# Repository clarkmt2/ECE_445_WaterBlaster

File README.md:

# ECE_445_WaterBlaster
Design, Firmware, and Documentation for Fully Electric Water Blaster

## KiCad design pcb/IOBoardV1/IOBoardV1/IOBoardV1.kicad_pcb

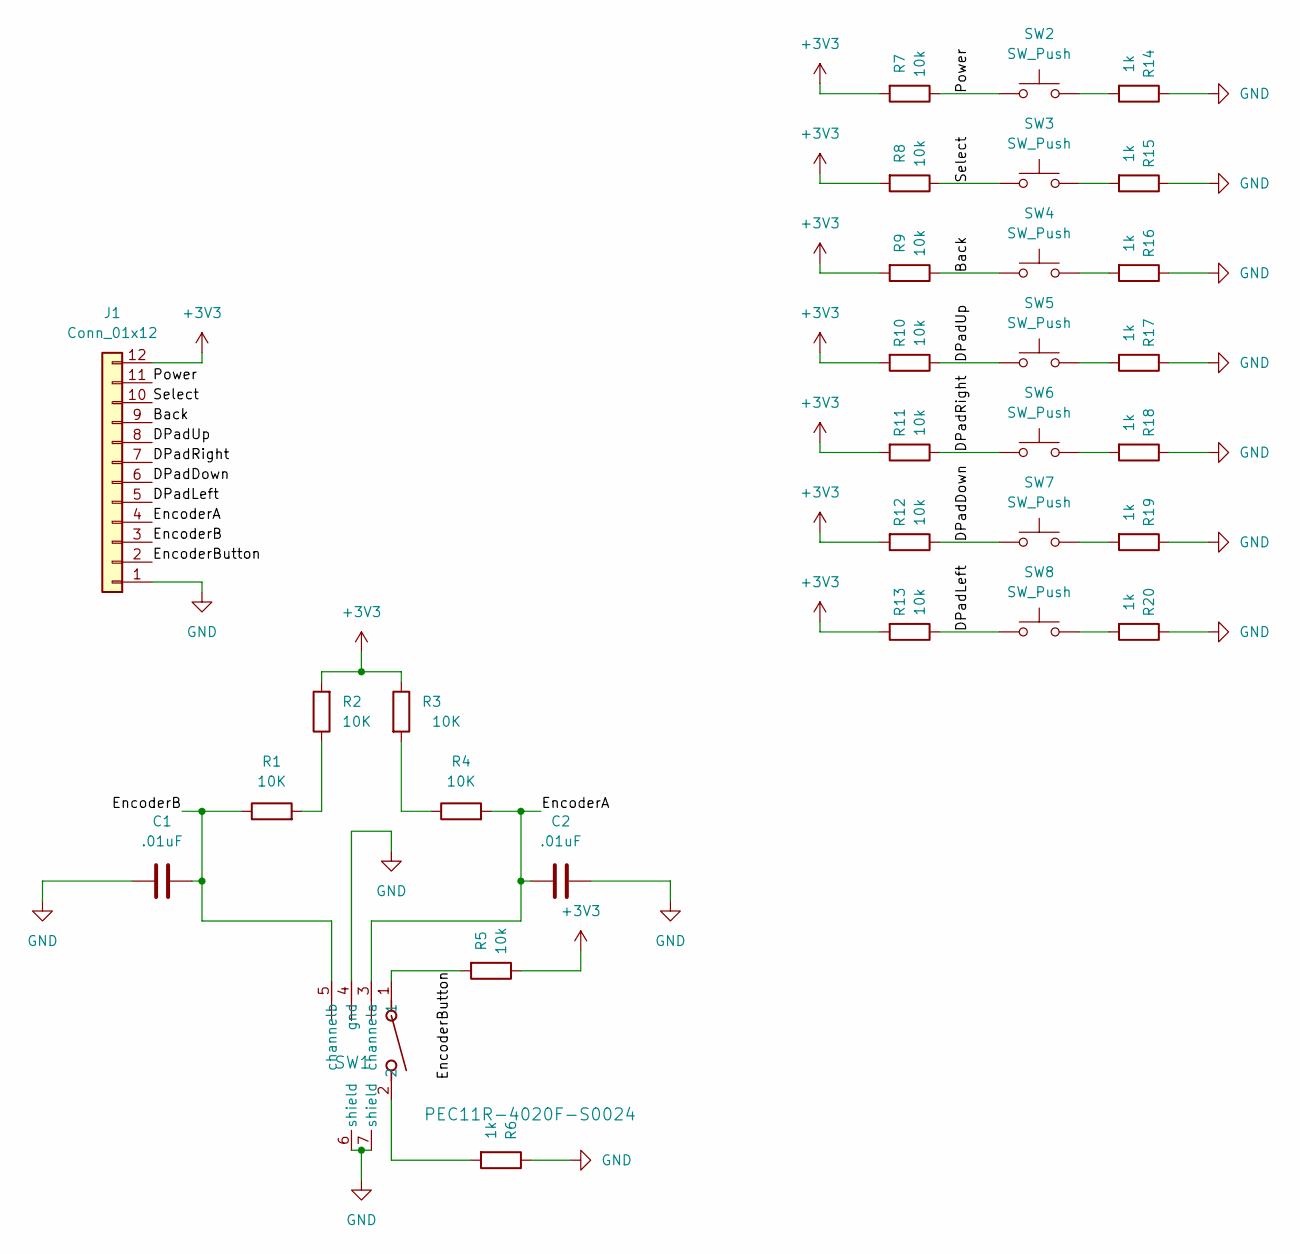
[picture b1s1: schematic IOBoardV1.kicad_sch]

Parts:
C1, C2: .01uF; C_0603_1608Metric_Pad1.08x0.95mm_HandSolder
J1: Conn_01x12; CONN_SD-43650-010_12_MOL
R1, R2, R3, R4: 10K; R_0603_1608Metric_Pad0.98x0.95mm_HandSolder
R5, R7, R8, R9, R10, R11, R12, R13: 10k; R_0603_1608Metric_Pad0.98x0.95mm_HandSolder; MPN RES SMD 10K OHM 5% 1/10W 0603
R6, R14, R15, R16, R17, R18, R19, R20: 1k; R_0603_1608Metric_Pad0.98x0.95mm_HandSolder; MPN RES SMD 1K OHM 5% 1/10W 0603
SW1: PEC11R-4020F-S0024; SW_PEC11R-4XXXK-SXXXX_BRN
SW2, SW3, SW4, SW5, SW6, SW7, SW8: SW_Push; PTS645SL43SMTR92LFS_CNK

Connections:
+3V3: J1.12, R2.2, R3.1, R5.1, R7.2, R8.2, R9.2, R10.2, R11.2, R12.2, R13.2
/Back: J1.9, R9.1, SW4.1
/DPadDown: J1.6, R12.1, SW7.1
/DPadLeft: J1.5, R13.1, SW8.1
/DPadRight: J1.7, R11.1, SW6.1
/DPadUp: J1.8, R10.1, SW5.1
/EncoderA: C2.1, J1.4, R4.2, SW1.3 (channela)
/EncoderB: C1.2, J1.3, R1.1, SW1.5 (channelb)
/EncoderButton: J1.2, R5.2, SW1.1
/Power: J1.11, R7.1, SW2.1
/Select: J1.10, R8.1, SW3.1
GND: C1.1, C2.2, J1.1, R6.1, R14.1, R15.1, R16.1, R17.1, R18.1, R19.1, R20.1, SW1.4 (gnd), SW1.6 (shield), SW1.7 (shield)
unnamed: R1.2, R2.1
unnamed: R3.2, R4.1
unnamed: R6.2, SW1.2
unnamed: R14.2, SW2.2
unnamed: R15.2, SW3.2
unnamed: R16.2, SW4.2
unnamed: R17.2, SW5.2
unnamed: R18.2, SW6.2
unnamed: R19.2, SW7.2
unnamed: R20.2, SW8.2

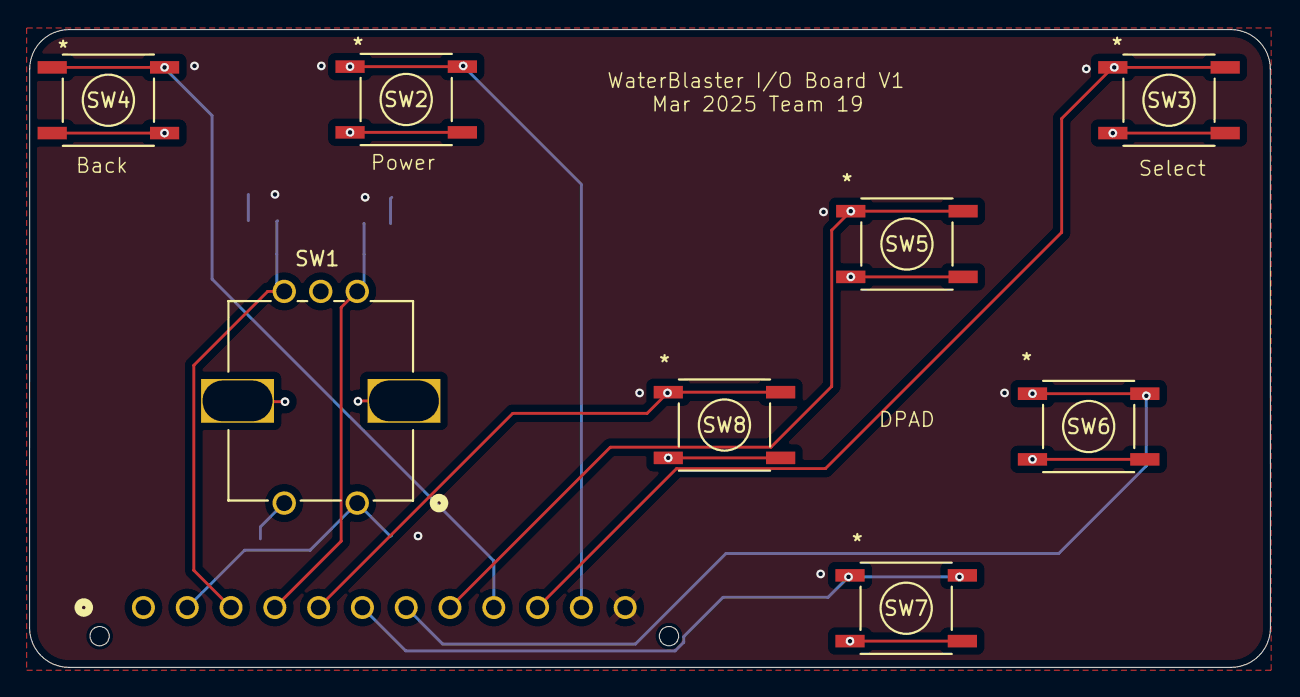
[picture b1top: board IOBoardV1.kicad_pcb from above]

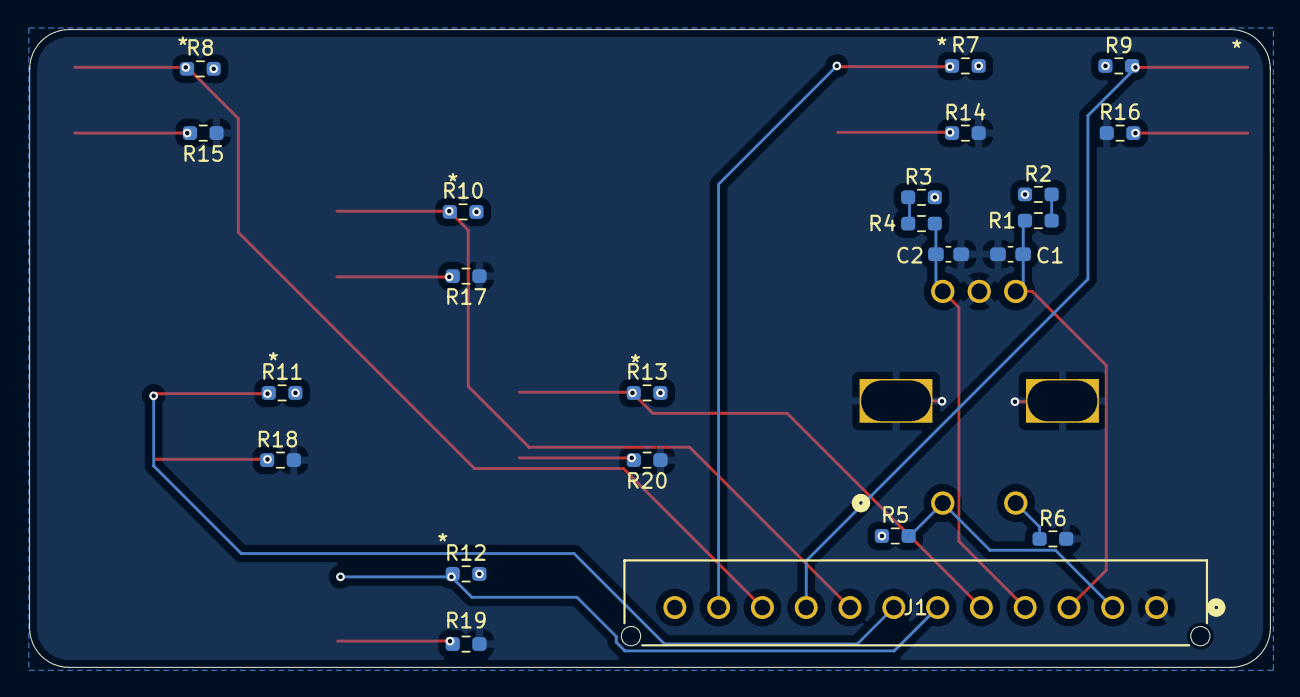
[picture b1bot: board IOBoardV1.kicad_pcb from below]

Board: 2 copper layers, 85.0 x 43.7 mm, 31 parts (23 on the bottom side), 22 nets.

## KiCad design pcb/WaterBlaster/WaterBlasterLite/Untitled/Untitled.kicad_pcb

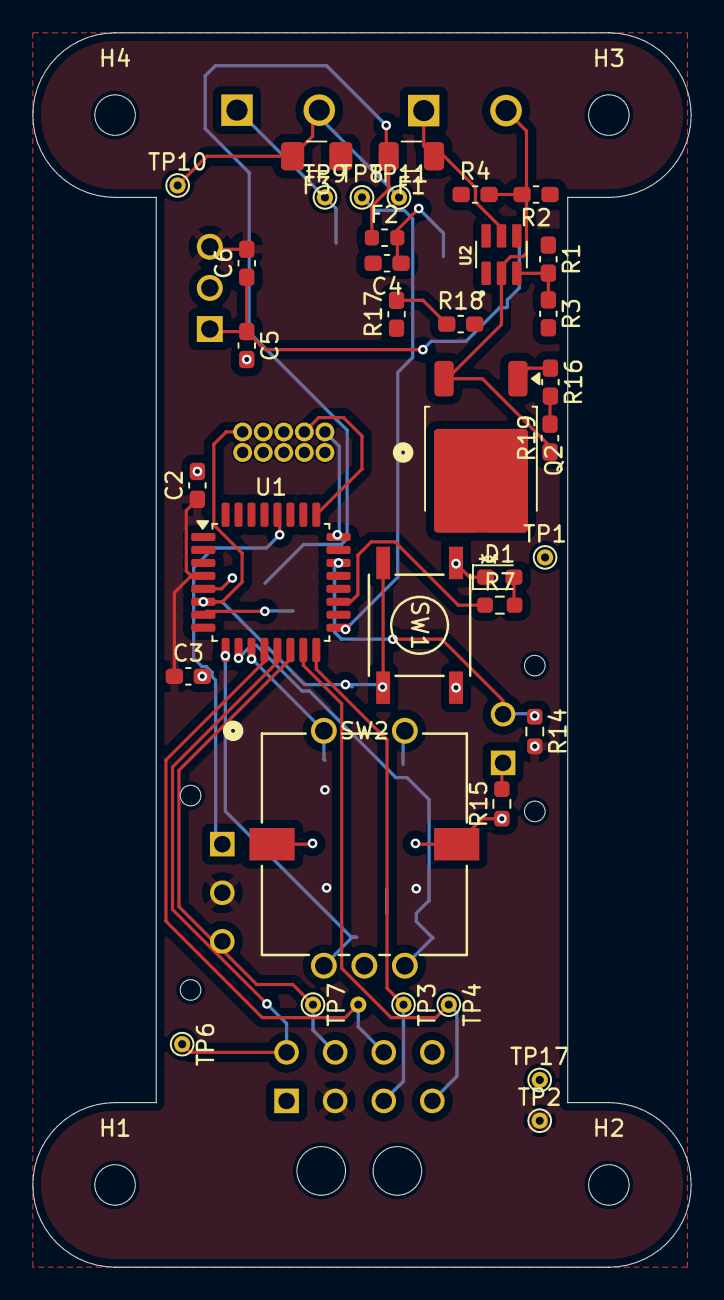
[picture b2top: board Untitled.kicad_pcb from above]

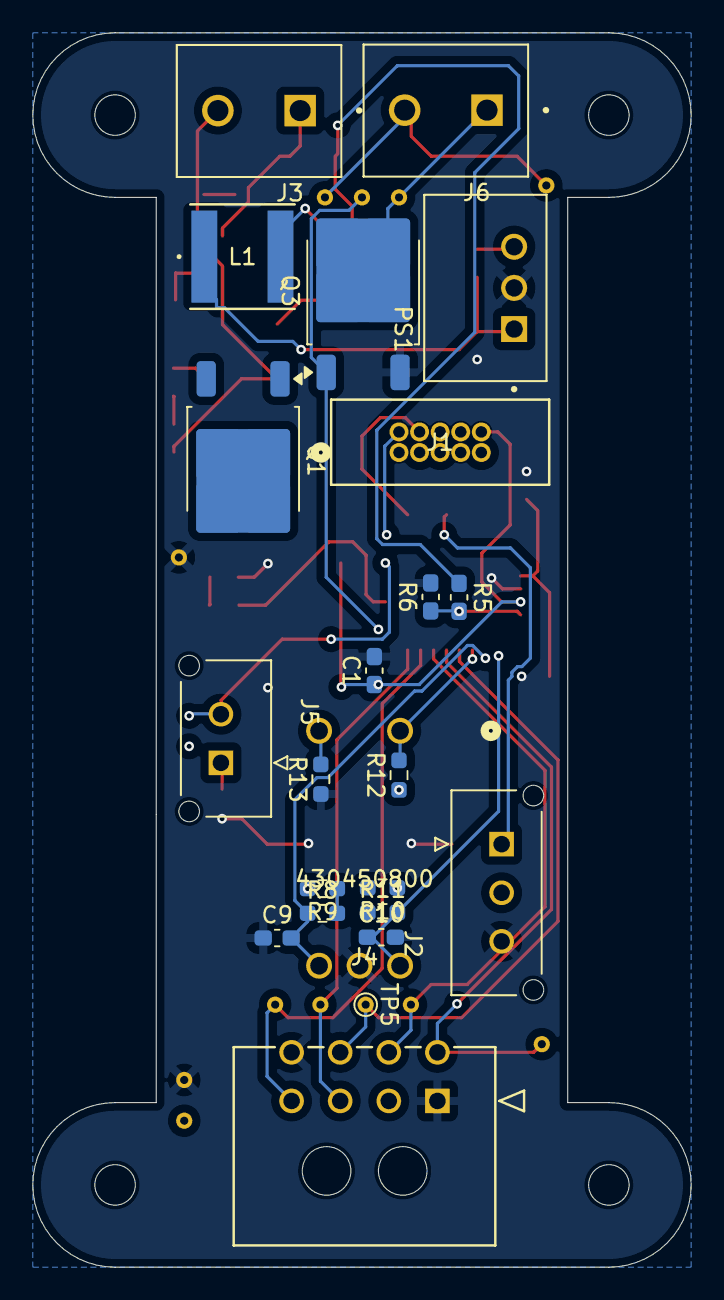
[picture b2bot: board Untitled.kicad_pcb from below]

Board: 2 copper layers, 40.6 x 76.2 mm, 62 parts (22 on the bottom side), 36 nets.

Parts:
C1: .1UF; C_0603_1608Metric_Pad1.08x0.95mm_HandSolder
C2: 100nF; C_0603_1608Metric_Pad1.08x0.95mm_HandSolder
C3: 4.7uF; C_0603_1608Metric_Pad1.08x0.95mm_HandSolder
C4, C5: 10uF; C_0603_1608Metric_Pad1.08x0.95mm_HandSolder
C6: 1nf; C_0603_1608Metric_Pad1.08x0.95mm_HandSolder
C9, C10: .01uF; C_0603_1608Metric_Pad1.08x0.95mm_HandSolder
D1: BLUE LED; LED_0603_1608Metric_Pad1.05x0.95mm_HandSolder
F1: 10A; Fuse_1206_3216Metric
F2: Fuse; Fuse_0603_1608Metric
F3: 6A; Fuse_1206_3216Metric_Pad1.42x1.75mm_HandSolder
H1, H2, H3, H4: MountingHole; MountingHole_2.5mm
J1: JTAG_Header; CONN_3220-10-0100-00_CNC
J2: Conn_01x03; MOLEX_436500317
J3: Conn_01x03; PHOENIX_1985865
J4: 430450800; CON_430450800_MOL
J5: Conn_01x02; MOLEX_436500227
J6: Conn_01x02; PHOENIX_1985865
L1: NR6028T101M; IND_TAIYO_NR6028_TAY
PS1: R-78K3.3-0.5; CONV_R-78K3.3-0.5
Q1, Q2, Q3: 353-MCU60N02-TPCT-ND; TO-252-2
R1: 62K; C_0603_1608Metric_Pad1.08x0.95mm_HandSolder
R2: 92K; C_0603_1608Metric_Pad1.08x0.95mm_HandSolder
R3: 2.7K; C_0603_1608Metric_Pad1.08x0.95mm_HandSolder
R4: 2.2K; C_0603_1608Metric_Pad1.08x0.95mm_HandSolder
R5: 40k; C_0603_1608Metric_Pad1.08x0.95mm_HandSolder
R6: 10k; C_0603_1608Metric_Pad1.08x0.95mm_HandSolder
R7, R13, R15: 1k; R_0603_1608Metric_Pad0.98x0.95mm_HandSolder
R8, R9, R10, R11: 10K; R_0603_1608Metric_Pad0.98x0.95mm_HandSolder
R12, R14: 10k; R_0603_1608Metric_Pad0.98x0.95mm_HandSolder
R16, R17, R18, R19: 10K; C_0603_1608Metric_Pad1.08x0.95mm_HandSolder
SW1: SW_Push; PTS645SL43SMTR92LFS_CNK
SW2: PEC11R-4020F-S0024; SW_PEC11R-4XXXK-SXXXX_BRN
TP1, TP17: GND; TestPoint_THTPad_D1.0mm_Drill0.5mm
TP2: 3V3; TestPoint_THTPad_D1.0mm_Drill0.5mm
TP3: ~{RESET}; TestPoint_THTPad_D1.0mm_Drill0.5mm
TP4: ~{CS}; TestPoint_THTPad_D1.0mm_Drill0.5mm
TP5: SCK; TestPoint_THTPad_D1.0mm_Drill0.5mm
TP6: MOSI; TestPoint_THTPad_D1.0mm_Drill0.5mm
TP7: MISO; TestPoint_THTPad_D1.0mm_Drill0.5mm
TP8: PumpControl; TestPoint_THTPad_D1.0mm_Drill0.5mm
TP9: PumpGND; TestPoint_THTPad_D1.0mm_Drill0.5mm
TP10, TP11: PumpPWR; TestPoint_THTPad_D1.0mm_Drill0.5mm
U1: STM32G070KBT6; LQFP-32_7x7mm_P0.8mm
U2: TPS3700DDCR2; SOT95P280X110-6N

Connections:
+3V3: C2.1, C3.1, C6.2, J2.2, J4.2, PS1.3 (+VOUT), R9.2, R10.1, R12.1, R14.2, TP2.1, U1.4 (VDD/VDDA)
+12V: F1.2, F2.1, F3.1, R5.1
/Display/SCLK: J4.7, TP5.1, U1.12 (PA5)
/Display/SDI: J4.5, TP6.1, U1.13 (PA6)
/Display/SDO: J4.6, TP7.1, U1.14 (PA7)
/Display//CS: J4.4, TP4.1, U1.15 (PB0)
/Display//RESET: J4.3, TP3.1, U1.16 (PB1)
/IO/EncoderA: C10.1, R11.2, SW2.3 (channela), U1.9 (PA2)
/IO/EncoderB: C9.2, R8.1, SW2.5 (channelb), U1.10 (PA3)
/IO/EncoderButton: R12.2, SW2.1, U1.11 (PA4)
/IO/LED1: R7.1, U1.19 (PA9)
/IO/Trigger: J5.2, R14.1, U1.22 (PA11(PA9))
/LeakSensor/LeakSensor1: J2.1, U1.28 (PB4)
/MCU/BatteryVoltage: R5.2, R6.1, U1.7 (PA0)
/MCU/PumpControl: Q3.1 (G), TP8.1, U1.17 (PB2)
/MCU/RESET: C1.1, J1.10 (~RESET), SW1.2, U1.6 (~RST)
/MCU/SWCLK: J1.4 (TCLK), U1.25 (PA14-BOOT0)
/MCU/SWDIO: J1.2 (TMS), U1.24 (PA13)
/PowerProtection/GndIn: J3.2, Q2.3 (S), R3.2, R4.1, R19.1, U2.2 (GND)
/PowerProtection/PowerIn: F1.1, J3.1, R1.1, R2.1, R18.2, U2.5 (VDD)
GND: C1.2, C2.2, C3.2, C4.2, C5.2, C9.1, C10.2, D1.1 (K), J1.3 (GND), J1.5 (GND), J1.9 (GND), J2.3, J4.1, J4.8, PS1.2 (GND), Q3.3 (S), R6.2, R13.1, R15.1, SW1.1, SW2.4 (gnd), SW2.6 (shield), SW2.7 (shield), TP1.1, TP17.1, U1.5 (VSS/VSSA)
unnamed: C4.1, F2.2, L1.2
unnamed: D1.2 (A), R7.2
unnamed: J5.1, R15.2
unnamed: J6.1, Q3.2 (D), TP9.1
unnamed: F3.2, J6.2, TP10.1
unnamed: C5.1, C6.1, L1.1, PS1.1 (+VIN)
unnamed: Q1.1 (G), R17.1, U2.1 (OUTA)
unnamed: Q1.3 (S), Q2.2 (D)
unnamed: Q2.1 (G), R16.1, U2.6 (OUTB)
unnamed: R8.2, R9.1
unnamed: R10.2, R11.1
unnamed: R13.2, SW2.2
unnamed: R16.2, R17.2, R18.1, R19.2
unnamed: R1.2, R3.1, U2.3 (INA+)
unnamed: R2.2, R4.2, U2.4 (INB-)

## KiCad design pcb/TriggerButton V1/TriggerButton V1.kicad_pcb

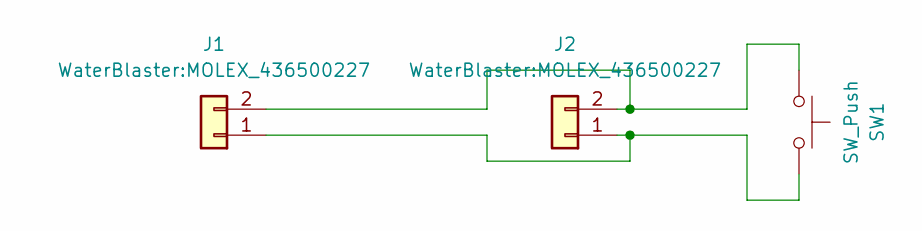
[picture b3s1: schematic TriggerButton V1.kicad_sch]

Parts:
J1, J2: WaterBlaster:MOLEX_436500227; MOLEX_436500227
SW1: SW_Push; PTS645SL43SMTR92LFS_CNK

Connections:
unnamed: J1.1, J2.1, SW1.2
unnamed: J1.2, J2.2, SW1.1

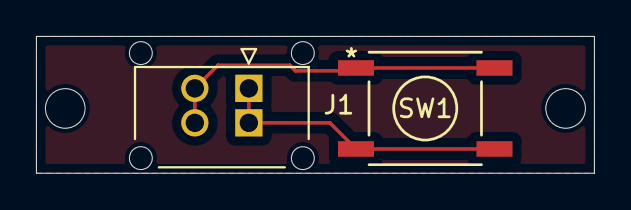
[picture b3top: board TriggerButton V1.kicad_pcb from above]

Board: 2 copper layers, 31.0 x 7.6 mm, 5 parts (1 on the bottom side), 2 nets.

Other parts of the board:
H1, H2: MountingHole; MountingHole_2.2mm_M2

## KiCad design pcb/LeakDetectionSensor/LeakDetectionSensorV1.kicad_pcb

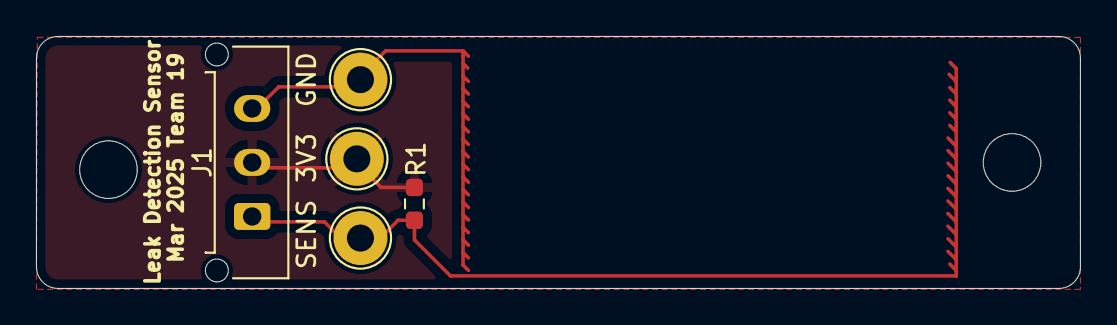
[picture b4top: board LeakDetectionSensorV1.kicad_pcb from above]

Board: 2 copper layers, 58.0 x 14.0 mm, 7 parts (0 on the bottom side), 3 nets.

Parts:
3V3: 3V3; TestPoint_Loop_D2.54mm_Drill1.5mm_Beaded
GND: GND; TestPoint_Loop_D2.54mm_Drill1.5mm_Beaded
H1, H2: MountingHole; MountingHole_3.2mm_M3
J1: Conn_01x03; Molex_Micro-Fit_3.0_43650-0315_1x03_P3.00mm_Vertical
R1: 1M; R_0603_1608Metric_Pad0.98x0.95mm_HandSolder
SENS: SENS; TestPoint_Loop_D2.54mm_Drill1.5mm_Beaded

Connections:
+3V3: 3V3.1, J1.2, R1.1
GND: GND.1, J1.3
unnamed: J1.1, R1.2, SENS.1

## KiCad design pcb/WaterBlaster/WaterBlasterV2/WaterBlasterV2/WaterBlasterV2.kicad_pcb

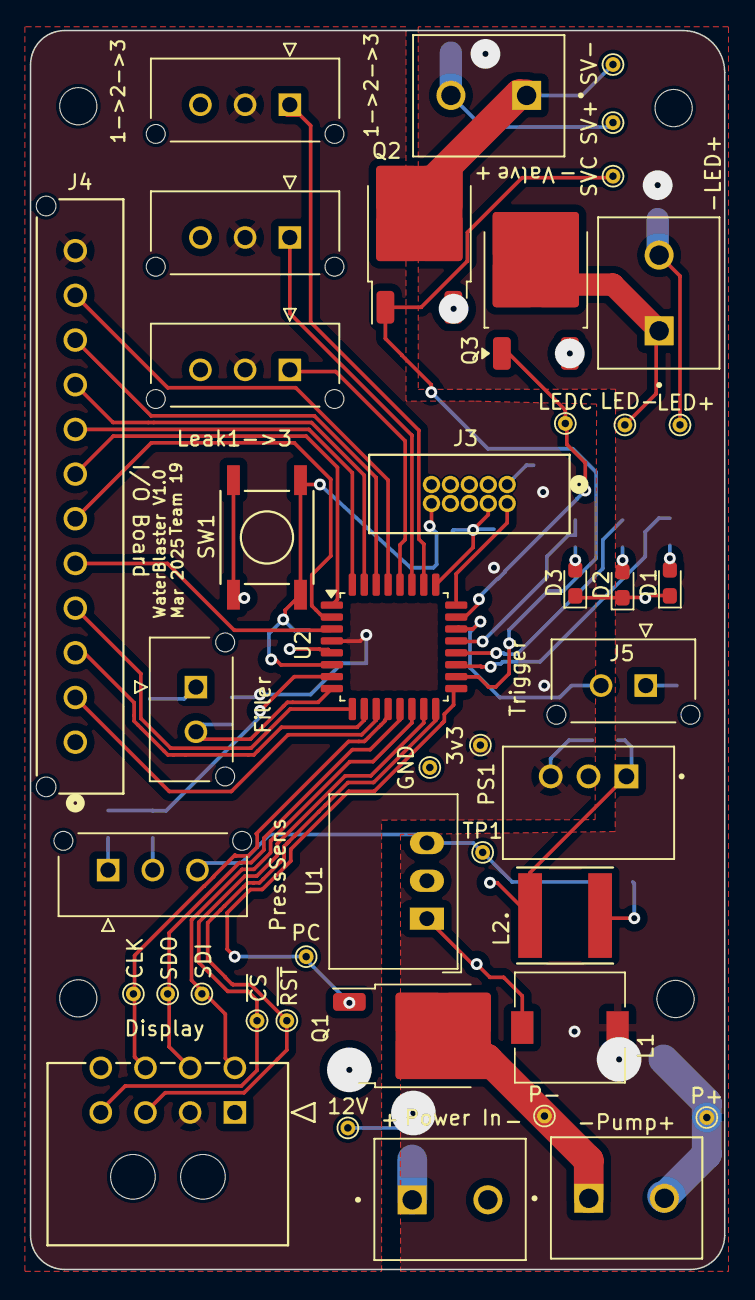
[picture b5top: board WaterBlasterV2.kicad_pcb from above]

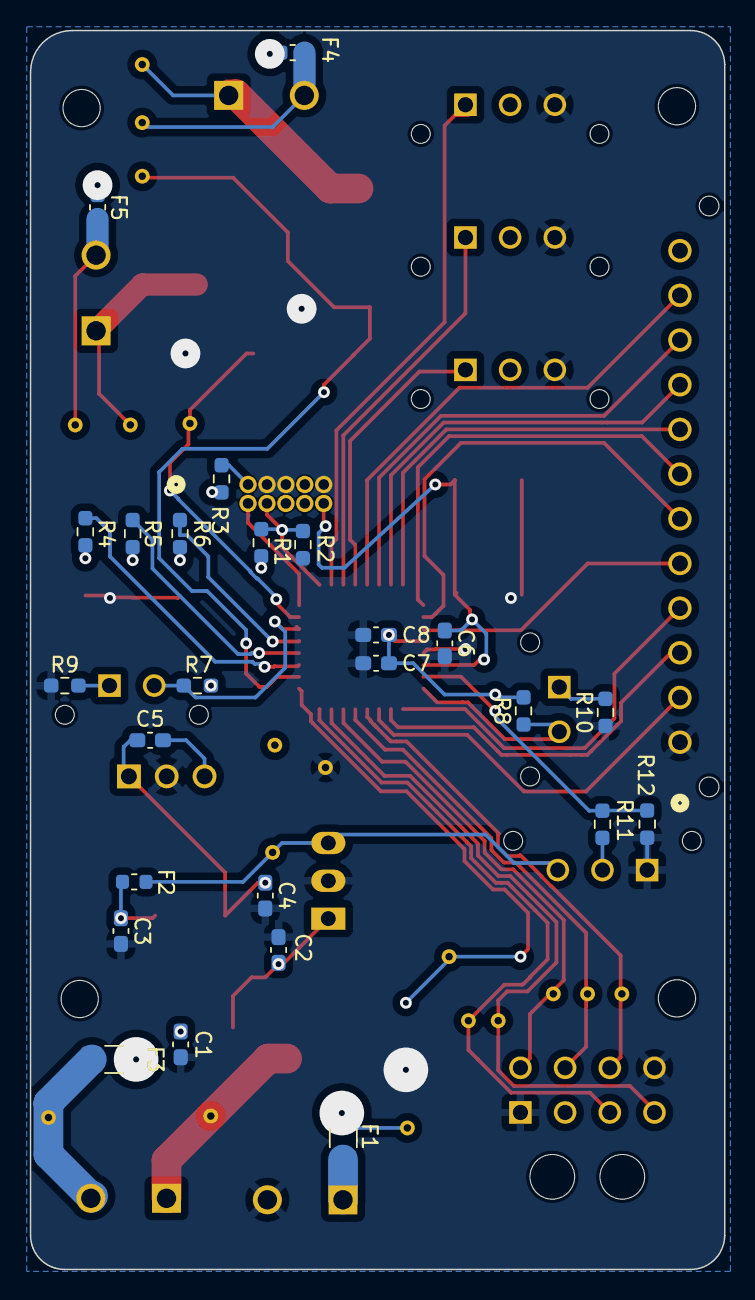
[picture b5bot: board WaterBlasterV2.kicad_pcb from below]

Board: 2 copper layers, 46.6 x 83.2 mm, 70 parts (28 on the bottom side), 51 nets.

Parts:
3v3: 3V3; TestPoint_THTPad_D1.0mm_Drill0.5mm
12V: 12V; TestPoint_THTPad_D1.0mm_Drill0.5mm
C1, C3, C4: 10uF; C_0603_1608Metric_Pad1.08x0.95mm_HandSolder
C2, C8: 4.7uF; C_0603_1608Metric_Pad1.08x0.95mm_HandSolder
C5: 1nf; C_0603_1608Metric_Pad1.08x0.95mm_HandSolder
C6: .1UF; C_0603_1608Metric_Pad1.08x0.95mm_HandSolder
C7: 100nF; C_0603_1608Metric_Pad1.08x0.95mm_HandSolder
CLK: SCK; TestPoint_THTPad_D1.0mm_Drill0.5mm
D1: BLUE LED; LED_0603_1608Metric_Pad1.05x0.95mm_HandSolder
D2: RED LED; LED_0603_1608Metric_Pad1.05x0.95mm_HandSolder
D3: YELLOW LED; LED_0603_1608Metric_Pad1.05x0.95mm_HandSolder
F1: 10A; Fuse_1206_3216Metric
F2: Fuse; Fuse_0603_1608Metric
F3: 6A; Fuse_1206_3216Metric_Pad1.42x1.75mm_HandSolder
F4, F5: 1.2A; Fuse_0603_1608Metric
Filler: Conn_01x02; MOLEX_436500227
GND: GND; TestPoint_THTPad_D1.0mm_Drill0.5mm
H1, H2, H3, H4: MountingHole; MountingHole_2.5mm
J1, J9, J14: Conn_01x03; PHOENIX_1985865
J2: 430450800; CON_430450800_MOL
J3: JTAG_Header; CONN_3220-10-0100-00_CNC
J4: Conn_01x12; CONN_SD-43650-010_12_MOL
J5: Conn_01x02; MOLEX_436500227
J7: Conn_01x02; PHOENIX_1985865
J10, J11, J13: Conn_01x03; MOLEX_436500317
L1: 12uH; L_7.3x7.3_H3.5
L2: NR6028T101M; IND_TAIYO_NR6028_TAY
LED+: LEDPWR; TestPoint_THTPad_D1.0mm_Drill0.5mm
LED-: LEDGND; TestPoint_THTPad_D1.0mm_Drill0.5mm
LEDC: LEDControl; TestPoint_THTPad_D1.0mm_Drill0.5mm
P+: PumpPWR; TestPoint_THTPad_D1.0mm_Drill0.5mm
P-: PumpGND; TestPoint_THTPad_D1.0mm_Drill0.5mm
PC: PumpControl; TestPoint_THTPad_D1.0mm_Drill0.5mm
PS1: R-78K3.3-0.5; CONV_R-78K3.3-0.5
PressSens: Conn_01x03; MOLEX_436500317
Q1, Q2, Q3: 353-MCU60N02-TPCT-ND; TO-252-2
R1, R2: R; R_0603_1608Metric_Pad0.98x0.95mm_HandSolder
R3: 0; R_0603_1608Metric_Pad0.98x0.95mm_HandSolder
R4, R5, R6, R9, R10: 1k; R_0603_1608Metric_Pad0.98x0.95mm_HandSolder
R7, R8: 10k; R_0603_1608Metric_Pad0.98x0.95mm_HandSolder
R11, R12: 10K; R_0603_1608Metric_Pad0.98x0.95mm_HandSolder
SDI: MOSI; TestPoint_THTPad_D1.0mm_Drill0.5mm
SDO: MISO; TestPoint_THTPad_D1.0mm_Drill0.5mm
SV+: ValvePWR; TestPoint_THTPad_D1.0mm_Drill0.5mm
SV-: ValveGND; TestPoint_THTPad_D1.0mm_Drill0.5mm
SVC: ValveControl; TestPoint_THTPad_D1.0mm_Drill0.5mm
SW1: SW_Push; PTS645SL43SMTR92LFS_CNK
TP1: 5v Protected; TestPoint_THTPad_D1.0mm_Drill0.5mm
U1: R-78E5.0-0.5; Converter_DCDC_RECOM_R-78E-0.5_THT
U2: STM32G070KBT6; LQFP-32_7x7mm_P0.8mm

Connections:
+3V3: 3v3.1, C5.2, C7.1, C8.1, J2.2, J4.12, J10.2, J11.2, J13.2, PS1.3 (+VOUT), R1.1, R3.1, R7.2, R8.2, U2.4 (VDD/VDDA)
+5V: F2.1, PressSens.3, TP1.1, U1.3 (OUT)
+12V: 12V.1, C1.1, F1.2, F3.1, F4.1, F5.1, L1.1
/Display/SCLK: CLK.1, J2.7, U2.12 (PA5)
/Display/SDI: J2.5, SDI.1, U2.14 (PA7)
/Display/SDO: J2.6, SDO.1, U2.13 (PA6)
/Display//CS: J2.4, U2.15 (PB0)
/Display//RESET: J2.3, U2.16 (PB1)
/IO/Back: J4.9, U2.31 (PB7)
/IO/DPadDown: J4.6, U2.2 (PC14-OSC32_IN)
/IO/DPadLeft: J4.5, U2.3 (PC15-OSC32_OUT)
/IO/DPadRight: J4.7, U2.1 (PB9)
/IO/DPadUp: J4.8, U2.32 (PB8)
/IO/EncoderA: J4.4, U2.9 (PA2)
/IO/EncoderB: J4.3, U2.10 (PA3)
/IO/EncoderButton: J4.2, U2.11 (PA4)
/IO/Filler: Filler.2, R8.1, U2.8 (PA1)
/IO/LED1: R4.1, U2.19 (PA9)
/IO/LED2: R5.1, U2.20 (PC6)
/IO/LED3: R6.1, U2.21 (PA10)
/IO/Power: J4.11, U2.29 (PB5)
/IO/Select: J4.10, U2.30 (PB6)
/IO/Trigger: J5.2, R7.1, U2.22 (PA11(PA9))
/MCU/LEDControl: LEDC.1, Q3.1 (G), U2.23 (PA12(PA10))
/MCU/LeakSensor1: J10.1, U2.28 (PB4)
/MCU/LeakSensor2: J11.1, U2.27 (PB3)
/MCU/LeakSensor3: J13.1, U2.26 (PA15)
/MCU/PressureTransducer: R11.1, R12.2, U2.7 (PA0)
/MCU/PumpControl: PC.1, Q1.1 (G), U2.17 (PB2)
/MCU/RESET: C6.1, J3.10 (~RESET), SW1.2, U2.6 (~RST)
/MCU/SWCLK: J3.4 (TCLK), R1.2, R2.2, U2.25 (PA14-BOOT0)
/MCU/SWDIO: J3.2 (TMS), U2.24 (PA13)
/MCU/ValveControl: Q2.1 (G), SVC.1, U2.18 (PA8)
GND: C1.2, C2.2, C3.2, C4.2, C6.2, C7.2, C8.2, D1.1 (K), D2.1 (K), D3.1 (K), GND.1, J1.2, J2.1, J2.8, J3.3 (GND), J3.5 (GND), J3.9 (GND), J4.1, J10.3, J11.3, J13.3, PS1.2 (GND), PressSens.1, Q1.3 (S), Q2.3 (S), Q3.3 (S), R2.1, R9.1, R10.1, R12.1, SW1.1, U1.2 (GND), U2.5 (VSS/VSSA)
unnamed: C3.1, F2.2, L2.2
unnamed: D1.2 (A), R4.2
unnamed: D2.2 (A), R5.2
unnamed: D3.2 (A), R6.2
unnamed: F1.1, J1.1
unnamed: J3.1 (VCC), R3.2
unnamed: J5.1, R9.2
unnamed: Filler.1, R10.2
unnamed: J7.1, P-.1, Q1.2 (D)
unnamed: F3.2, J7.2, P+.1
unnamed: J9.1, LED-.1, Q3.2 (D)
unnamed: F5.2, J9.2, LED+.1
unnamed: PressSens.2, R11.2
unnamed: J14.1, Q2.2 (D), SV-.1
unnamed: F4.2, J14.2, SV+.1
unnamed: C4.1, C5.1, L2.1, PS1.1 (+VIN)
unnamed: C2.1, L1.2, U1.1 (IN)

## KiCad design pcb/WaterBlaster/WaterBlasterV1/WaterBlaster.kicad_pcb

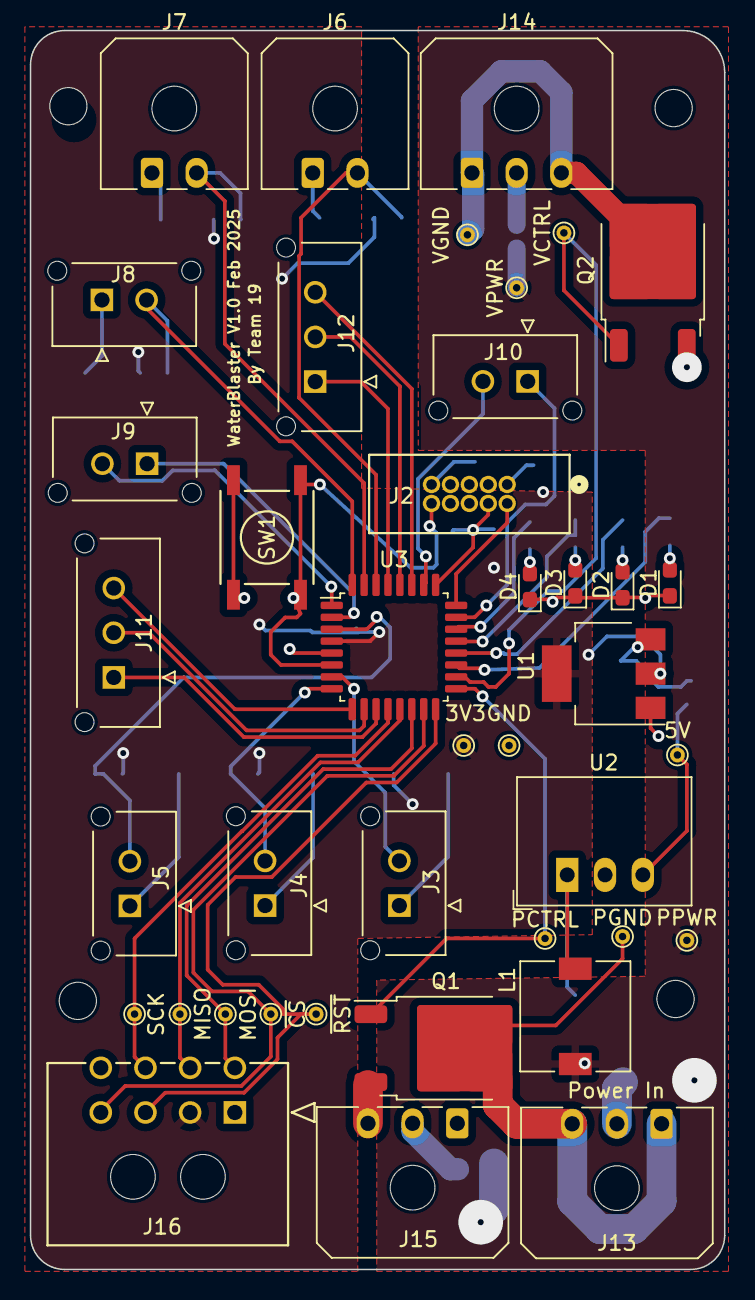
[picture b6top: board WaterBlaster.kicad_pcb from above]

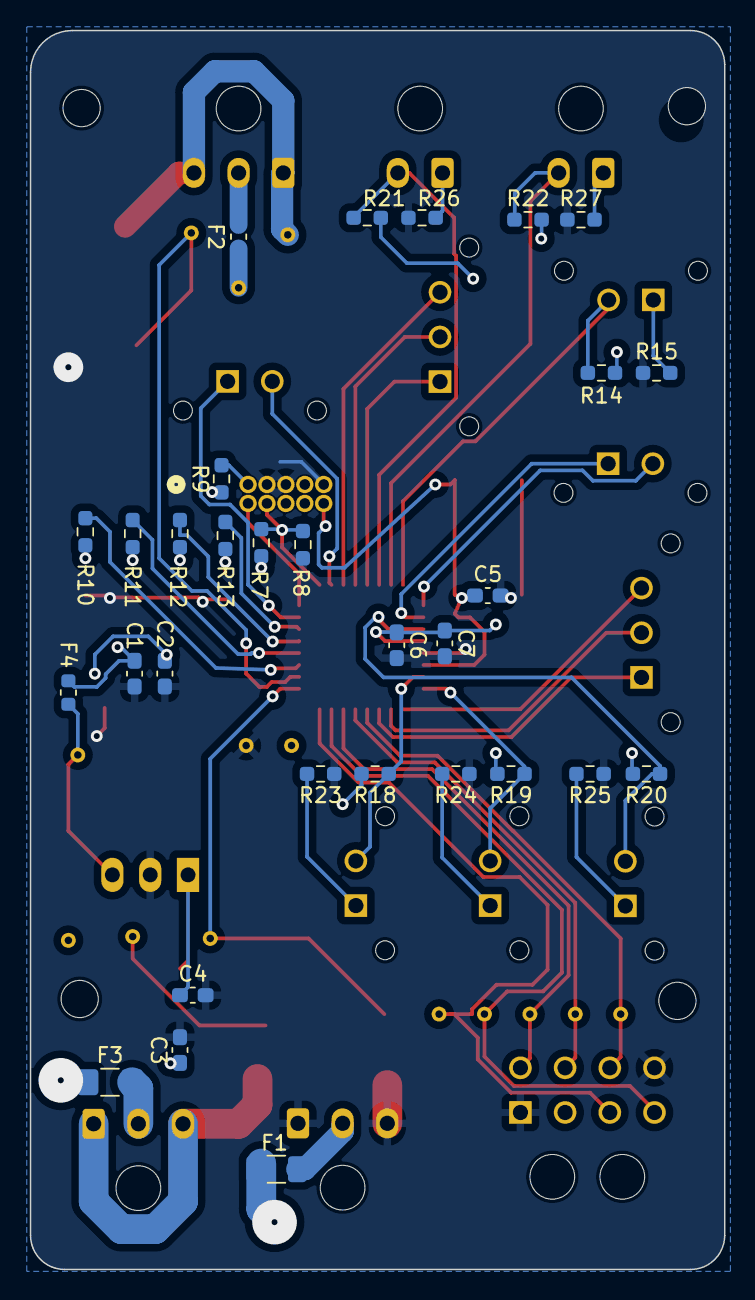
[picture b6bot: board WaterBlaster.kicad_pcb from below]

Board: 2 copper layers, 46.6 x 83.2 mm, 72 parts (33 on the bottom side), 51 nets.

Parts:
3V3: 3V3; TestPoint_THTPad_D1.0mm_Drill0.5mm
5V: 5v Protected; TestPoint_THTPad_D1.0mm_Drill0.5mm
C1, C2: 1.0uF; C_0603_1608Metric_Pad1.08x0.95mm_HandSolder
C3: 10uF; C_0603_1608Metric_Pad1.08x0.95mm_HandSolder
C4, C7: 4.7uF; C_0603_1608Metric_Pad1.08x0.95mm_HandSolder
C5: .1UF; C_0603_1608Metric_Pad1.08x0.95mm_HandSolder
C6: 100nF; C_0603_1608Metric_Pad1.08x0.95mm_HandSolder
D1: BLUE LED; LED_0603_1608Metric_Pad1.05x0.95mm_HandSolder
D2: RED LED; LED_0603_1608Metric_Pad1.05x0.95mm_HandSolder
D3: YELLOW LED; LED_0603_1608Metric_Pad1.05x0.95mm_HandSolder
D4: GREEN LED; LED_0603_1608Metric_Pad1.05x0.95mm_HandSolder
F1: 10A; Fuse_1206_3216Metric
F2: 1.2A; Fuse_0603_1608Metric
F3: 6A; Fuse_1206_3216Metric_Pad1.42x1.75mm_HandSolder
F4: Fuse; Fuse_0603_1608Metric
GND: GND; TestPoint_THTPad_D1.0mm_Drill0.5mm
H1, H2, H3, H4: MountingHole; MountingHole_2.5mm
J2: JTAG_Header; CONN_3220-10-0100-00_CNC
J3, J4, J5, J8, J10: Conn_01x02; MOLEX_436500227
J6, J7: Conn_01x02; Molex_Micro-Fit_3.0_43650-0200_1x02_P3.00mm_Horizontal
J9: WaterBlaster:MOLEX_436500227; MOLEX_436500227
J11, J12: Conn_01x03; MOLEX_436500317
J13, J14, J15: Conn_01x03; Molex_Micro-Fit_3.0_43650-0300_1x03_P3.00mm_Horizontal
J16: 430450800; CON_430450800_MOL
L1: 12uH; L_7.3x7.3_H3.5
MISO: MISO; TestPoint_THTPad_D1.0mm_Drill0.5mm
MOSI: MOSI; TestPoint_THTPad_D1.0mm_Drill0.5mm
PCTRL: PumpControl; TestPoint_THTPad_D1.0mm_Drill0.5mm
PGND: PumpGND; TestPoint_THTPad_D1.0mm_Drill0.5mm
PPWR: PumpPWR; TestPoint_THTPad_D1.0mm_Drill0.5mm
Q1, Q2: 353-MCU60N02-TPCT-ND; TO-252-2
R7, R8: R; R_0603_1608Metric_Pad0.98x0.95mm_HandSolder
R9: 0; R_0603_1608Metric_Pad0.98x0.95mm_HandSolder
R10, R11, R12, R13, R15, R23, R24, R25, R26, R27: 1k; R_0603_1608Metric_Pad0.98x0.95mm_HandSolder
R14, R18, R19, R20, R21, R22: 10k; R_0603_1608Metric_Pad0.98x0.95mm_HandSolder
SCK: SCK; TestPoint_THTPad_D1.0mm_Drill0.5mm
SW1: SW_Push; PTS645SL43SMTR92LFS_CNK
U1: AZ1117EH-3.3TRG1; SOT-223-3_TabPin2
U2: R-78E5.0-0.5; Converter_DCDC_RECOM_R-78E-0.5_THT
U3: STM32G070KBT6; LQFP-32_7x7mm_P0.8mm
VCTRL: ValveControl; TestPoint_THTPad_D1.0mm_Drill0.5mm
VGND: ValveGND; TestPoint_THTPad_D1.0mm_Drill0.5mm
VPWR: ValvePWR; TestPoint_THTPad_D1.0mm_Drill0.5mm

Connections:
+3V3: 3V3.1, C2.1, C6.1, C7.1, J16.2, R7.1, R9.1, R14.2, R18.2, R19.2, R20.2, R21.2, R22.2, U1.2 (VO), U3.4 (VDD/VDDA)
+5V: 5V.1, C1.1, F4.1, F4.2, U1.3 (VI), U2.3 (OUT)
+12V: C3.1, F1.2, F2.1, F3.1, L1.1, PPWR.1, VPWR.1
/Display/SCLK: J16.7, SCK.1, U3.12 (PA5)
/Display/SDI: J16.5, MOSI.1, U3.14 (PA7)
/Display/SDO: J16.6, MISO.1, U3.13 (PA6)
/Display//CS: J16.4, U3.15 (PB0)
/Display//RESET: J16.3, U3.16 (PB1)
/IO/Button1: J3.2, R18.1, U3.7 (PA0)
/IO/Button2: J4.2, R19.1, U3.8 (PA1)
/IO/Button3: J5.2, R20.1, U3.3 (PC15-OSC32_OUT)
/IO/Button4: J6.2, R21.1, U3.30 (PB6)
/IO/Button5: J7.2, R22.1, U3.31 (PB7)
/IO/Button6: J8.2, R14.1, U3.32 (PB8)
/IO/LED1: R10.1, U3.19 (PA9)
/IO/LED2: R11.1, U3.20 (PC6)
/IO/LED3: R12.1, U3.21 (PA10)
/IO/LED4: R13.1, U3.22 (PA11(PA9))
/MCU/ExtraConn_1_1: J10.1, U3.23 (PA12(PA10))
/MCU/ExtraConn_1_2: J10.2, U3.26 (PA15)
/MCU/ExtraConn_2_1: J9.2, U3.1 (PB9)
/MCU/ExtraConn_2_2: J9.1, U3.2 (PC14-OSC32_IN)
/MCU/ExtraConn_3_1: J11.3, U3.9 (PA2)
/MCU/ExtraConn_3_2: J11.2, U3.10 (PA3)
/MCU/ExtraConn_3_3: J11.1, U3.11 (PA4)
/MCU/ExtraConn_4_1: J12.3, U3.27 (PB3)
/MCU/ExtraConn_4_2: J12.2, U3.28 (PB4)
/MCU/ExtraConn_4_3: J12.1, U3.29 (PB5)
/MCU/PumpControl: PCTRL.1, Q1.1 (G), U3.17 (PB2)
/MCU/RESET: C5.1, J2.10 (~RESET), SW1.2, U3.6 (~RST)
/MCU/SWCLK: J2.4 (TCLK), R7.2, R8.2, U3.25 (PA14-BOOT0)
/MCU/SWDIO: J2.2 (TMS), U3.24 (PA13)
/MCU/ValveControl: Q2.1 (G), U3.18 (PA8), VCTRL.1
GND: C1.2, C2.2, C3.2, C4.2, C5.2, C6.2, C7.2, D1.1 (K), D2.1 (K), D3.1 (K), D4.1 (K), GND.1, J2.3 (GND), J2.5 (GND), J2.9 (GND), J15.1, J15.3, J16.1, J16.8, Q1.3 (S), Q2.3 (S), R8.1, R15.1, R23.1, R24.1, R25.1, R26.1, R27.1, SW1.1, U1.1 (GND), U2.2 (GND), U3.5 (VSS/VSSA)
unnamed: D1.2 (A), R10.2
unnamed: D2.2 (A), R11.2
unnamed: D3.2 (A), R12.2
unnamed: D4.2 (A), R13.2
unnamed: J2.1 (VCC), R9.2
unnamed: J3.1, R23.2
unnamed: J4.1, R24.2
unnamed: J5.1, R25.2
unnamed: J6.1, R26.2
unnamed: J7.1, R27.2
unnamed: J8.1, R15.2
unnamed: J13.1, J13.3, PGND.1, Q1.2 (D)
unnamed: F3.2, J13.2
unnamed: J14.1, J14.3, Q2.2 (D), VGND.1
unnamed: F2.2, J14.2
unnamed: F1.1, J15.2
unnamed: C4.1, L1.2, U2.1 (IN)

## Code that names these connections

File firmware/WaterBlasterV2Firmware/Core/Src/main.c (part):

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    // Immediately stop everything
    HAL_GPIO_WritePin(GPIOA, GPIO_PIN_8, GPIO_PIN_RESET); // valve closed
    HAL_GPIO_WritePin(GPIOB, GPIO_PIN_2, GPIO_PIN_RESET); // pump off
    HAL_GPIO_WritePin(GPIOA, GPIO_PIN_9, GPIO_PIN_RESET); // LED1 off
    HAL_GPIO_WritePin(GPIOA, GPIO_PIN_10, GPIO_PIN_RESET); // LED2 off
    HAL_GPIO_WritePin(GPIOC, GPIO_PIN_6, GPIO_PIN_RESET); // LED3 off

    clear_buffer();
    pad_center(Buffer[1], "!! LEAK DETECTED !!");
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
    NHD_OLED_displayOff(); // Turn off OLED after 5 sec

    // Now sit here doing nothing until a reset button (e.g., PB3) is pressed
    while (HAL_GPIO_ReadPin(GPIOB, GPIO_PIN_6) == GPIO_PIN_SET) {
        // Waiting for PB3 to be pressed
        HAL_Delay(10);
    }

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		// Immediately stop everything
		HAL_GPIO_WritePin(GPIOA, GPIO_PIN_8, GPIO_PIN_RESET); // valve closed
		HAL_GPIO_WritePin(GPIOB, GPIO_PIN_2, GPIO_PIN_RESET); // pump off
		HAL_GPIO_WritePin(GPIOA, GPIO_PIN_9, GPIO_PIN_RESET); // LED1 off
		HAL_GPIO_WritePin(GPIOA, GPIO_PIN_10, GPIO_PIN_RESET); // LED2 off
		HAL_GPIO_WritePin(GPIOC, GPIO_PIN_6, GPIO_PIN_RESET); // LED3 off

		clear_buffer();
		pad_center(Buffer[1], "!! LEAK DETECTED !!");
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
		NHD_OLED_displayOff(); // Turn off OLED after 5 sec

		// Now sit here doing nothing until a reset button (e.g., PB3) is pressed
		while (HAL_GPIO_ReadPin(GPIOB, GPIO_PIN_7) == GPIO_PIN_SET) {
			// Waiting for PB3 to be pressed
			HAL_Delay(10);
		}

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    HAL_GPIO_WritePin(GPIOA, GPIO_PIN_10, GPIO_PIN_SET);
    HAL_GPIO_WritePin(GPIOC, GPIO_PIN_6, GPIO_PIN_SET);

    // Force PB5 to be input with no pull
    GPIO_InitTypeDef GPIO_InitStruct = {0};
    GPIO_InitStruct.Pin = GPIO_PIN_5;
    GPIO_InitStruct.Mode = GPIO_MODE_INPUT;
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
			        // ======= Button handling: (THIS IS THE IMPORTANT PART) =======

			        // PA4 pressed (encoder button) → select setting
			        if (HAL_GPIO_ReadPin(GPIOA, GPIO_PIN_4) == GPIO_PIN_RESET && pressed == 0) {
			            pressed = 1;
			            page = settings_selection + 2; // Enter selected setting page
			            break;
			        }

			        // PB5 pressed (exit button) → go back to home
			        if (HAL_GPIO_ReadPin(GPIOB, GPIO_PIN_5) == GPIO_PIN_RESET && pressed == 0) {
			            pressed = 1;
			            page = 0; // Back to Home Page
			            break;
			        }

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  /*Configure GPIO pin Output Level */
  HAL_GPIO_WritePin(GPIOC, GPIO_PIN_6, GPIO_PIN_RESET);

  /*Configure GPIO pins : PB9 PB3 PB4 PB5
                           PB6 PB7 PB8 */
  GPIO_InitStruct.Pin = GPIO_PIN_9|GPIO_PIN_3|GPIO_PIN_4|GPIO_PIN_5
                          |GPIO_PIN_6|GPIO_PIN_7|GPIO_PIN_8;
  GPIO_InitStruct.Mode = GPIO_MODE_INPUT;
  GPIO_InitStruct.Pull = GPIO_NOPULL;
  HAL_GPIO_Init(GPIOB, &GPIO_InitStruct);

  /*Configure GPIO pins : PC14 PC15 */
  GPIO_InitStruct.Pin = GPIO_PIN_14|GPIO_PIN_15;
  GPIO_InitStruct.Mode = GPIO_MODE_INPUT;
  GPIO_InitStruct.Pull = GPIO_NOPULL;
  HAL_GPIO_Init(GPIOC, &GPIO_InitStruct);

  /*Configure GPIO pins : PA1 PA2 PA3 PA4
                           PA6 PA11 PA15 */
  GPIO_InitStruct.Pin = GPIO_PIN_1|GPIO_PIN_2|GPIO_PIN_3|GPIO_PIN_4
                          |GPIO_PIN_6|GPIO_PIN_11|GPIO_PIN_15;
  GPIO_InitStruct.Mode = GPIO_MODE_INPUT;
  GPIO_InitStruct.Pull = GPIO_NOPULL;
  HAL_GPIO_Init(GPIOA, &GPIO_InitStruct);

  /*Configure GPIO pins : PA5 PA7 PA8 PA9
                           PA10 PA12 */
  GPIO_InitStruct.Pin = GPIO_PIN_5|GPIO_PIN_7|GPIO_PIN_8|GPIO_PIN_9
                          |GPIO_PIN_10|GPIO_PIN_12;
  GPIO_InitStruct.Mode = GPIO_MODE_OUTPUT_PP;
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  GPIO_InitStruct.Speed = GPIO_SPEED_FREQ_LOW;
  HAL_GPIO_Init(GPIOA, &GPIO_InitStruct);

  /*Configure GPIO pins : PB0 PB1 PB2 */
  GPIO_InitStruct.Pin = GPIO_PIN_0|GPIO_PIN_1|GPIO_PIN_2;
  GPIO_InitStruct.Mode = GPIO_MODE_OUTPUT_PP;
  GPIO_InitStruct.Pull = GPIO_NOPULL;
  GPIO_InitStruct.Speed = GPIO_SPEED_FREQ_LOW;
  HAL_GPIO_Init(GPIOB, &GPIO_InitStruct);

  /*Configure GPIO pin : PC6 */
  GPIO_InitStruct.Pin = GPIO_PIN_6;
  GPIO_InitStruct.Mode = GPIO_MODE_OUTPUT_PP;
  GPIO_InitStruct.Pull = GPIO_NOPULL;
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
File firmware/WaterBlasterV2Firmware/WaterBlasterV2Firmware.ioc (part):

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Mcu.Name=STM32G070KBTx
Mcu.Package=LQFP32
Mcu.UserName=STM32G070KBTx
PA0.Mode=IN0
PA0.Signal=ADC1_IN0
PA1.Signal=GPIO_Input
PA10.Signal=GPIO_Output
PA11\ [PA9].Signal=GPIO_Input
PA12\ [PA10].Signal=GPIO_Output
PA13.Mode=Serial_Wire
PA13.Signal=SYS_SWDIO
PA14-BOOT0.Mode=Serial_Wire
PA14-BOOT0.Signal=SYS_SWCLK
PA15.Signal=GPIO_Input
PA2.Signal=GPIO_Input
PA3.Signal=GPIO_Input
PA4.Signal=GPIO_Input
PA5.Signal=GPIO_Output
PA6.Signal=GPIO_Input
PA7.Signal=GPIO_Output
PA8.Signal=GPIO_Output
PA9.Signal=GPIO_Output
PB0.Signal=GPIO_Output
PB1.Signal=GPIO_Output
PB2.Signal=GPIO_Output
PB3.Signal=GPIO_Input
PB4.Signal=GPIO_Input
PB5.Signal=GPIO_Input
PB6.Signal=GPIO_Input
PB7.Signal=GPIO_Input
PB8.Signal=GPIO_Input
PB9.Signal=GPIO_Input
PC14-OSC32_IN\ (PC14).Signal=GPIO_Input
PC15-OSC32_OUT\ (PC15).Signal=GPIO_Input
PC6.Signal=GPIO_Output
RCC.HSE_VALUE=8000000
RCC.SYSCLKFreq_VALUE=16000000
board=custom

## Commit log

2025-02-11 Updating Structure
2025-02-11 Add files via upload
    Preliminary Block Diagram
2025-02-11 Rename BlockDiagramWaterBlaster.drawio (1).png to BlockDiagram
2025-02-11 Rename BlockDiagram to BlockDiagram.png
2025-02-11 Rename VisualAid.drawio.png to VisualAid.png
2025-02-19 Create Design Review
2025-02-19 Create test
2025-03-04 Pushing complete PCB
2025-03-04 Initial Firmware Commit
2025-03-13 Updating firmware and CAD
2025-03-23 Creating Leak Sensor, Code Push, V2 PCB adding support for LEDs, Pressure Transducer, and IO Board, switched high current to use screw terminals, added 3v3 DCDC instead of LDO
2025-03-25 created IO board, leak detection sensor, and trigger board
2025-03-25 Rename Image from iOS (1).jpg to SketchOfPreliminaryDesign.jpg
2025-04-08 V2 Firmware
2025-04-12 Update main.c for version 2
2025-04-20 Big CAD Commit
2025-04-22 Updated shit
2025-04-22 Updated the firmware, working very well
2025-04-27 added hella CAD
2025-04-29 Firmware updates
2025-04-29 updated firmware
2025-04-29 almost demo fw
2025-05-02 Updating firmware and PCB
2025-05-02 Updated naming
2025-05-08 Update notebook.txt
    Updated notebook with context, final commit
2025-05-08 Update notebook.txt
    fixed spaces

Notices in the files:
firmware/WaterBlasterV2Firmware/Core/Src/main.c:
Copyright (c) 2025 STMicroelectronics.
All rights reserved.
This software is licensed under terms that can be found in the LICENSE file
